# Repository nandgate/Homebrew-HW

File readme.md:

Hardware files for the 8-bit homebrew project.

* Each folder contains the KiCad project for a processor/board.
* Under the PLD there is a folder with the WinCUPL projects for the PLD for each board.

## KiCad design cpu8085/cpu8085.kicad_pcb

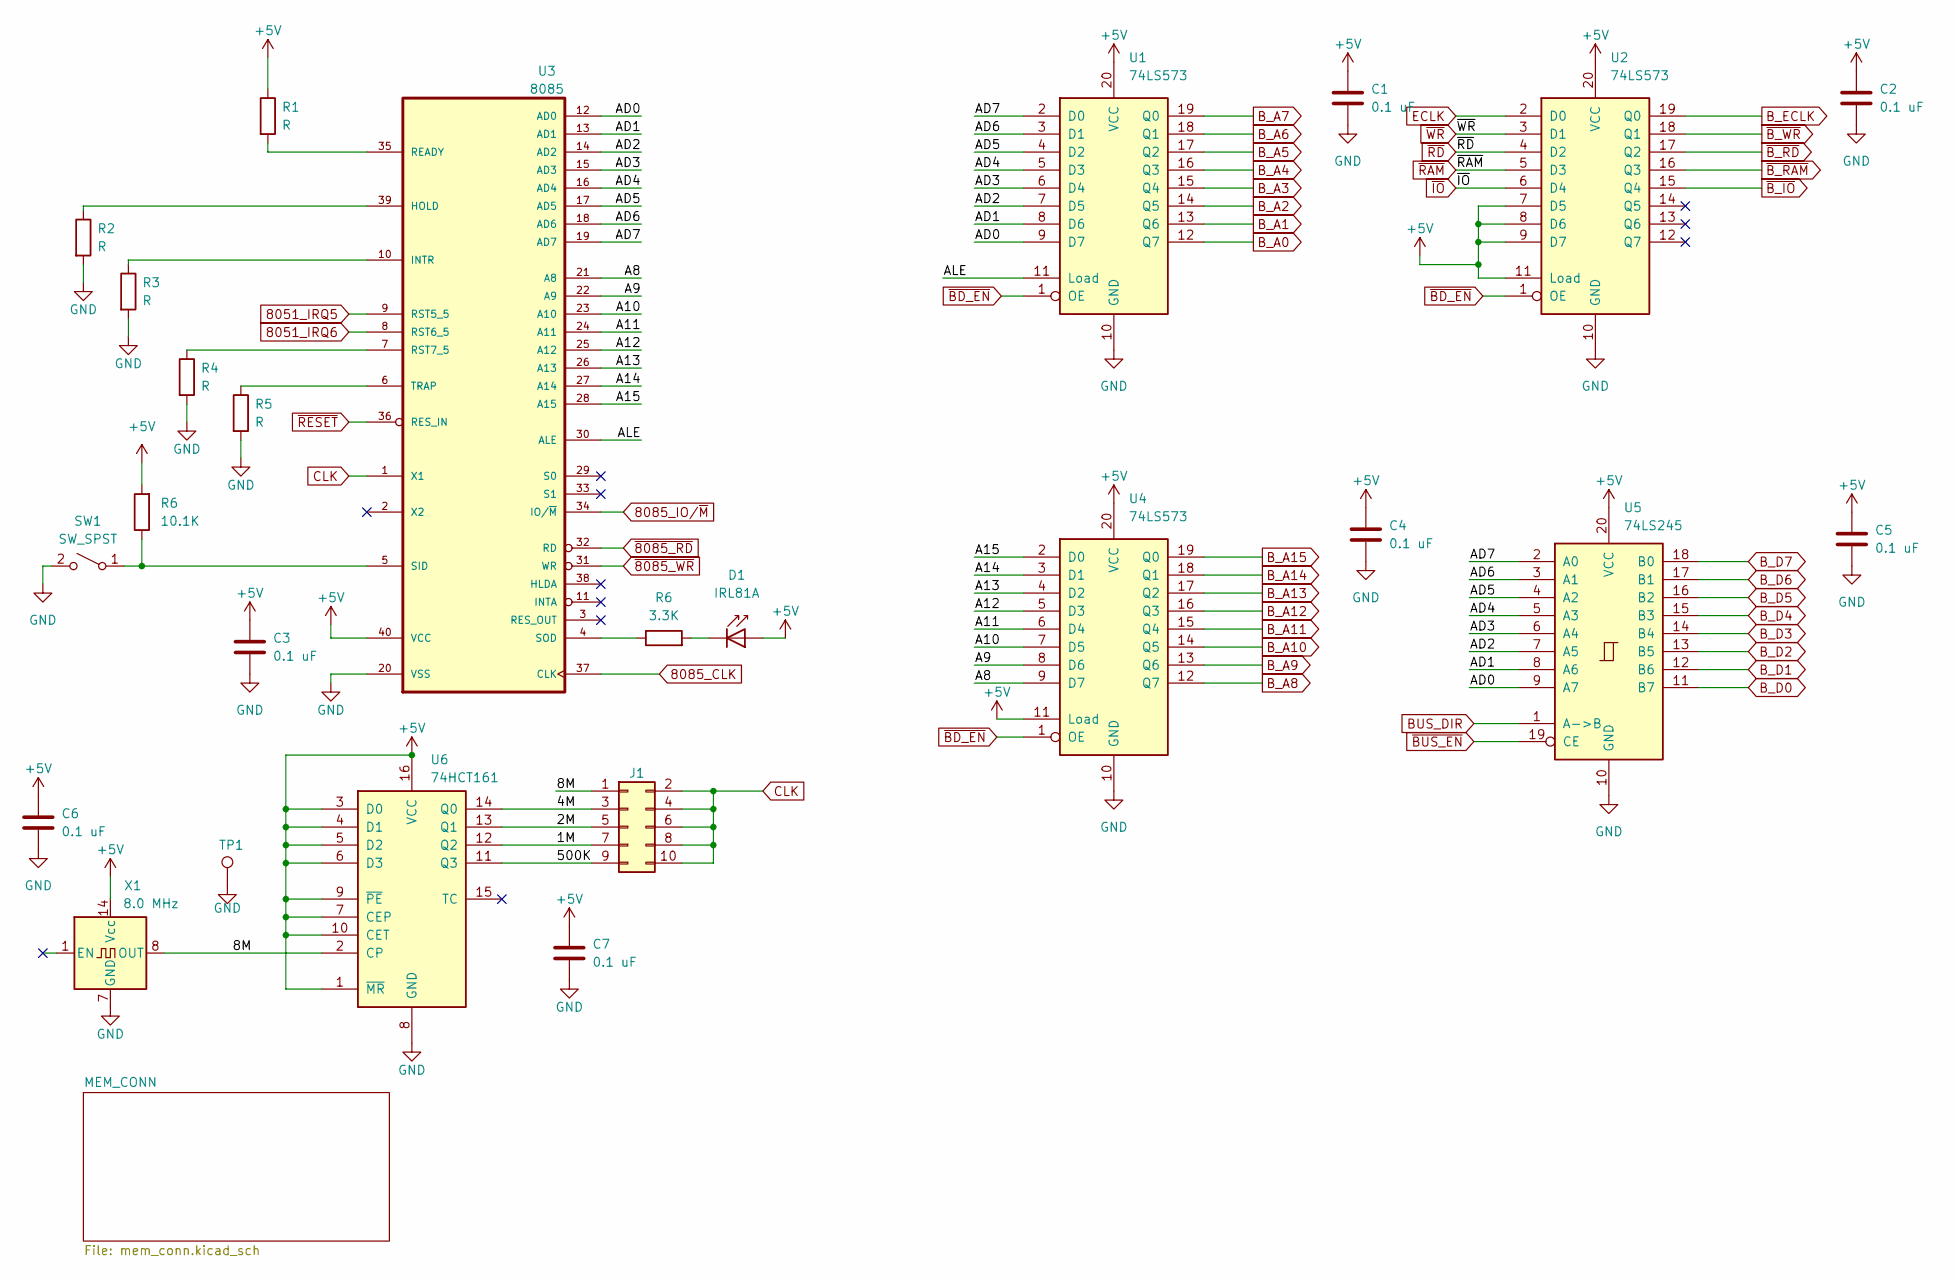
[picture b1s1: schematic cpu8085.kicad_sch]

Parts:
C1, C2, C3, C4, C5, C6, C7: 0.1 uF; C_Rect_L7.2mm_W3.0mm_P5.00mm_FKS2_FKP2_MKS2_MKP2
D1: IRL81A; LED_D5.0mm
J1: Conn_02x05_Odd_Even; PinHeader_2x05_P2.54mm_Vertical
R1, R2, R3, R4, R5: R; R_Axial_DIN0207_L6.3mm_D2.5mm_P10.16mm_Horizontal
R6: 10.1K; R_Axial_DIN0207_L6.3mm_D2.5mm_P10.16mm_Horizontal
SW1: SW_SPST; SW_DIP_SPSTx01_Slide_9.78x4.72mm_W7.62mm_P2.54mm
TP1: TestPoint; TestPoint_Pad_2.0x2.0mm
U1, U2, U4: 74LS573; DIP-20_W7.62mm
U3: 8085; DIP-40_W15.24mm_Socket
U5: 74LS245; DIP-20_W7.62mm
U6: 74HCT161; DIP-16_W7.62mm
X1: 8.0 MHz; Oscillator_DIP-14

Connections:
8051_IRQ5: U3.9 (RST5_5); also elsewhere on the board
8051_IRQ6: U3.8 (RST6_5); also elsewhere on the board
8085_CLK: U3.37 (CLK); also elsewhere on the board
8085_IO/~M: U3.34 (IO/~M); also elsewhere on the board
/1M: J1.7, U6.12 (Q2)
/2M: J1.5, U6.13 (Q1)
/4M: J1.3, U6.14 (Q0)
/8M: J1.1, U6.2 (CP), X1.8 (OUT)
/500K: J1.9, U6.11 (Q3)
/A8: U3.21 (A8), U4.9 (D7)
/A9: U3.22 (A9), U4.8 (D6)
/A10: U3.23 (A10), U4.7 (D5)
/A11: U3.24 (A11), U4.6 (D4)
/A12: U3.25 (A12), U4.5 (D3)
/A13: U3.26 (A13), U4.4 (D2)
/A14: U3.27 (A14), U4.3 (D1)
/A15: U3.28 (A15), U4.2 (D0)
/AD0: U1.9 (D7), U3.12 (AD0), U5.9 (A7)
/AD1: U1.8 (D6), U3.13 (AD1), U5.8 (A6)
/AD2: U1.7 (D5), U3.14 (AD2), U5.7 (A5)
/AD3: U1.6 (D4), U3.15 (AD3), U5.6 (A4)
/AD4: U1.5 (D3), U3.16 (AD4), U5.5 (A3)
/AD5: U1.4 (D2), U3.17 (AD5), U5.4 (A2)
/AD6: U1.3 (D1), U3.18 (AD6), U5.3 (A1)
/AD7: U1.2 (D0), U3.19 (AD7), U5.2 (A0)
/ALE: U1.11 (Load), U3.30 (ALE)
BUS_DIR: U5.1 (A->B); also elsewhere on the board
B_A0: U1.12 (Q7); also elsewhere on the board
B_A1: U1.13 (Q6); also elsewhere on the board
B_A2: U1.14 (Q5); also elsewhere on the board
B_A3: U1.15 (Q4); also elsewhere on the board
B_A4: U1.16 (Q3); also elsewhere on the board
B_A5: U1.17 (Q2); also elsewhere on the board
B_A6: U1.18 (Q1); also elsewhere on the board
B_A7: U1.19 (Q0); also elsewhere on the board
B_A8: U4.12 (Q7); also elsewhere on the board
B_A9: U4.13 (Q6); also elsewhere on the board
B_A10: U4.14 (Q5); also elsewhere on the board
B_A11: U4.15 (Q4); also elsewhere on the board
B_A12: U4.16 (Q3); also elsewhere on the board
B_A13: U4.17 (Q2); also elsewhere on the board
B_A14: U4.18 (Q1); also elsewhere on the board
B_A15: U4.19 (Q0); also elsewhere on the board
B_D0: U5.11 (B7); also elsewhere on the board
B_D1: U5.12 (B6); also elsewhere on the board
B_D2: U5.13 (B5); also elsewhere on the board
B_D3: U5.14 (B4); also elsewhere on the board
B_D4: U5.15 (B3); also elsewhere on the board
B_D5: U5.16 (B2); also elsewhere on the board
B_D6: U5.17 (B1); also elsewhere on the board
B_D7: U5.18 (B0); also elsewhere on the board
B_ECLK: U2.19 (Q0); also elsewhere on the board
CLK: J1.2, J1.4, J1.6, J1.8, J1.10, U3.1 (X1)
ECLK: U2.2 (D0); also elsewhere on the board
GND: C1.2, C2.2, C3.2, C4.2, C5.2, C6.2, C7.2, R2.2, R3.2, R4.2, R5.2, SW1.2 (B), TP1.1, U1.10 (GND), U2.10 (GND), U3.20 (VSS), U4.10 (GND), U5.10 (GND), U6.8 (GND), X1.7 (GND); also elsewhere on the board
unnamed: R2.1, U3.39 (HOLD)
unnamed: R3.1, U3.10 (INTR)
unnamed: R1.2, U3.35 (READY)
unnamed: R4.1, U3.7 (RST7_5)
unnamed: R5.1, U3.6 (TRAP)
~8085_RD: U3.32 (RD); also elsewhere on the board
~8085_WR: U3.31 (WR); also elsewhere on the board
~BD_EN: U1.1 (OE), U2.1 (OE), U4.1 (OE); also elsewhere on the board
~BUS_EN: U5.19 (CE); also elsewhere on the board
~B_IO: U2.15 (Q4); also elsewhere on the board
~B_RAM: U2.16 (Q3); also elsewhere on the board
~B_RD: U2.17 (Q2); also elsewhere on the board
~B_WR: U2.18 (Q1); also elsewhere on the board
~IO: U2.6 (D4); also elsewhere on the board
~RAM: U2.5 (D3); also elsewhere on the board
~RD: U2.4 (D2); also elsewhere on the board
~RESET: U3.36 (RES_IN); also elsewhere on the board
~WR: U2.3 (D1); also elsewhere on the board

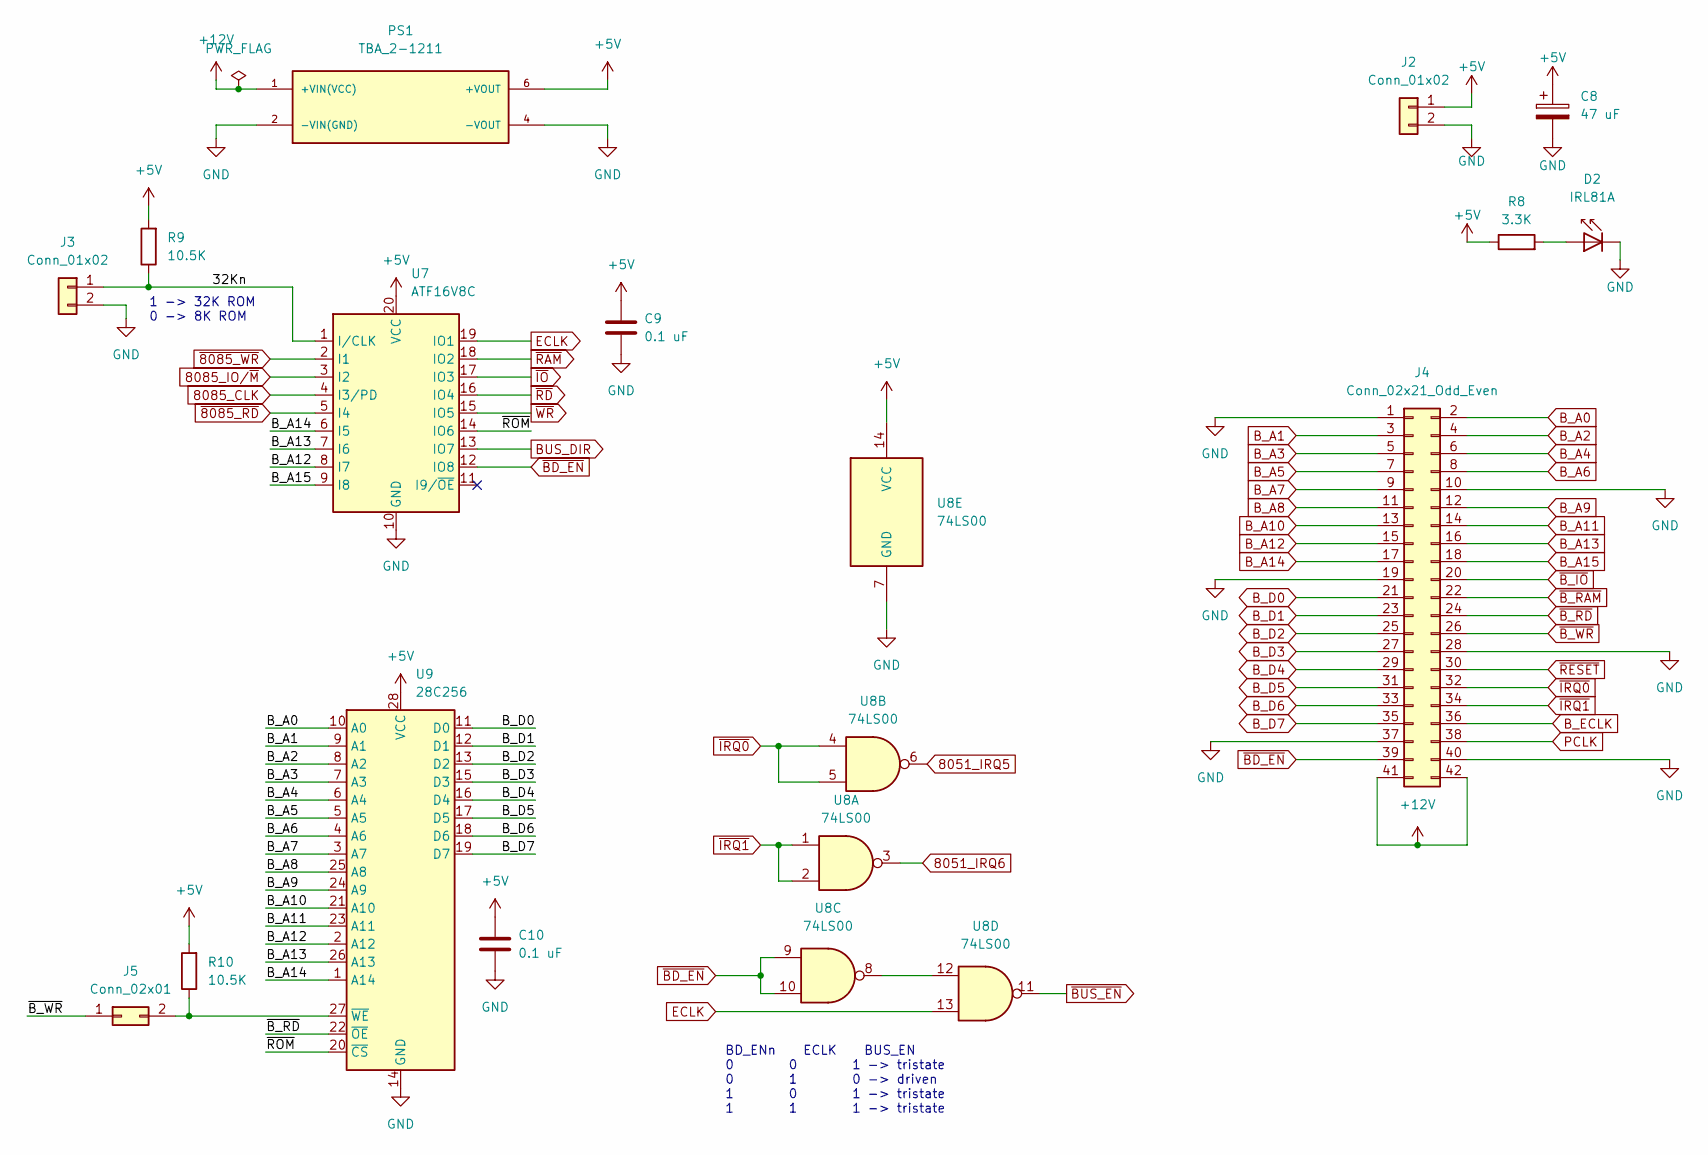
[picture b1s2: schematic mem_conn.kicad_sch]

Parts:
C8: 47 uF; CP_Radial_D5.0mm_P2.00mm
C9, C10: 0.1 uF; C_Rect_L7.2mm_W3.0mm_P5.00mm_FKS2_FKP2_MKS2_MKP2
D2: IRL81A; LED_D5.0mm
J2, J3: Conn_01x02; PinHeader_1x02_P2.54mm_Vertical
J4: Conn_02x21_Odd_Even; PinHeader_2x21_P2.54mm_Vertical
J5: Conn_02x01; PinHeader_1x02_P2.54mm_Vertical
PS1: TBA_2-1211; CONV_TBA_2-1211; PARTREV April 19, 2021
R8: 3.3K; R_Axial_DIN0207_L6.3mm_D2.5mm_P10.16mm_Horizontal
R9, R10: 10.5K; R_Axial_DIN0207_L6.3mm_D2.5mm_P10.16mm_Horizontal
U7: ATF16V8C; DIP-20_W7.62mm
U8: 74LS00; DIP-14_W7.62mm
U9: 28C256; DIP-28_W15.24mm

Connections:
8051_IRQ5: U8.6; also elsewhere on the board
8051_IRQ6: U8.3; also elsewhere on the board
8085_CLK: U7.4 (I3/PD); also elsewhere on the board
8085_IO/~M: U7.3 (I2); also elsewhere on the board
+12V: J4.41, J4.42, PS1.1 (+VIN(VCC))
/MEM_CONN/32Kn: J3.1, R9.1, U7.1 (I/CLK)
/MEM_CONN/~ROM: U7.14 (IO6), U9.20 (~CS)
BUS_DIR: U7.13 (IO7); also elsewhere on the board
B_A0: J4.2, U9.10 (A0); also elsewhere on the board
B_A1: J4.3, U9.9 (A1); also elsewhere on the board
B_A2: J4.4, U9.8 (A2); also elsewhere on the board
B_A3: J4.5, U9.7 (A3); also elsewhere on the board
B_A4: J4.6, U9.6 (A4); also elsewhere on the board
B_A5: J4.7, U9.5 (A5); also elsewhere on the board
B_A6: J4.8, U9.4 (A6); also elsewhere on the board
B_A7: J4.9, U9.3 (A7); also elsewhere on the board
B_A8: J4.11, U9.25 (A8); also elsewhere on the board
B_A9: J4.12, U9.24 (A9); also elsewhere on the board
B_A10: J4.13, U9.21 (A10); also elsewhere on the board
B_A11: J4.14, U9.23 (A11); also elsewhere on the board
B_A12: J4.15, U7.8 (I7), U9.2 (A12); also elsewhere on the board
B_A13: J4.16, U7.7 (I6), U9.26 (A13); also elsewhere on the board
B_A14: J4.17, U7.6 (I5), U9.1 (A14); also elsewhere on the board
B_A15: J4.18, U7.9 (I8); also elsewhere on the board
B_D0: J4.21, U9.11 (D0); also elsewhere on the board
B_D1: J4.23, U9.12 (D1); also elsewhere on the board
B_D2: J4.25, U9.13 (D2); also elsewhere on the board
B_D3: J4.27, U9.15 (D3); also elsewhere on the board
B_D4: J4.29, U9.16 (D4); also elsewhere on the board
B_D5: J4.31, U9.17 (D5); also elsewhere on the board
B_D6: J4.33, U9.18 (D6); also elsewhere on the board
B_D7: J4.35, U9.19 (D7); also elsewhere on the board
B_ECLK: J4.36; also elsewhere on the board
ECLK: U7.19 (IO1), U8.13; also elsewhere on the board
GND: C8.2, C9.2, C10.2, D2.1 (K), J2.2, J3.2, J4.1, J4.10, J4.19, J4.28, J4.37, J4.40, PS1.2 (-VIN(GND)), PS1.4 (-VOUT), U7.10 (GND), U8.7 (GND), U9.14 (GND); also elsewhere on the board
unnamed: D2.2 (A), R8.2
unnamed: J5.2, R10.1, U9.27 (~WE)
unnamed: U8.8, U8.12
PCLK: J4.38
~8085_RD: U7.5 (I4); also elsewhere on the board
~8085_WR: U7.2 (I1); also elsewhere on the board
~BD_EN: J4.39, U7.12 (IO8), U8.9, U8.10; also elsewhere on the board
~BUS_EN: U8.11; also elsewhere on the board
~B_IO: J4.20; also elsewhere on the board
~B_RAM: J4.22; also elsewhere on the board
~B_RD: J4.24, U9.22 (~OE); also elsewhere on the board
~B_WR: J4.26, J5.1; also elsewhere on the board
~IO: U7.17 (IO3); also elsewhere on the board
~IRQ0: J4.32, U8.4, U8.5
~IRQ1: J4.34, U8.1, U8.2
~RAM: U7.18 (IO2); also elsewhere on the board
~RD: U7.16 (IO4); also elsewhere on the board
~RESET: J4.30; also elsewhere on the board
~WR: U7.15 (IO5); also elsewhere on the board

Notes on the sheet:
1 -> 32K ROM 0 -> 8K ROM
BD_ENn ECLK BUS_EN 0 0 1 -> tristate 0 1 0 -> driven 1 0 1 -> tristate 1 1 1 -> tristate

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
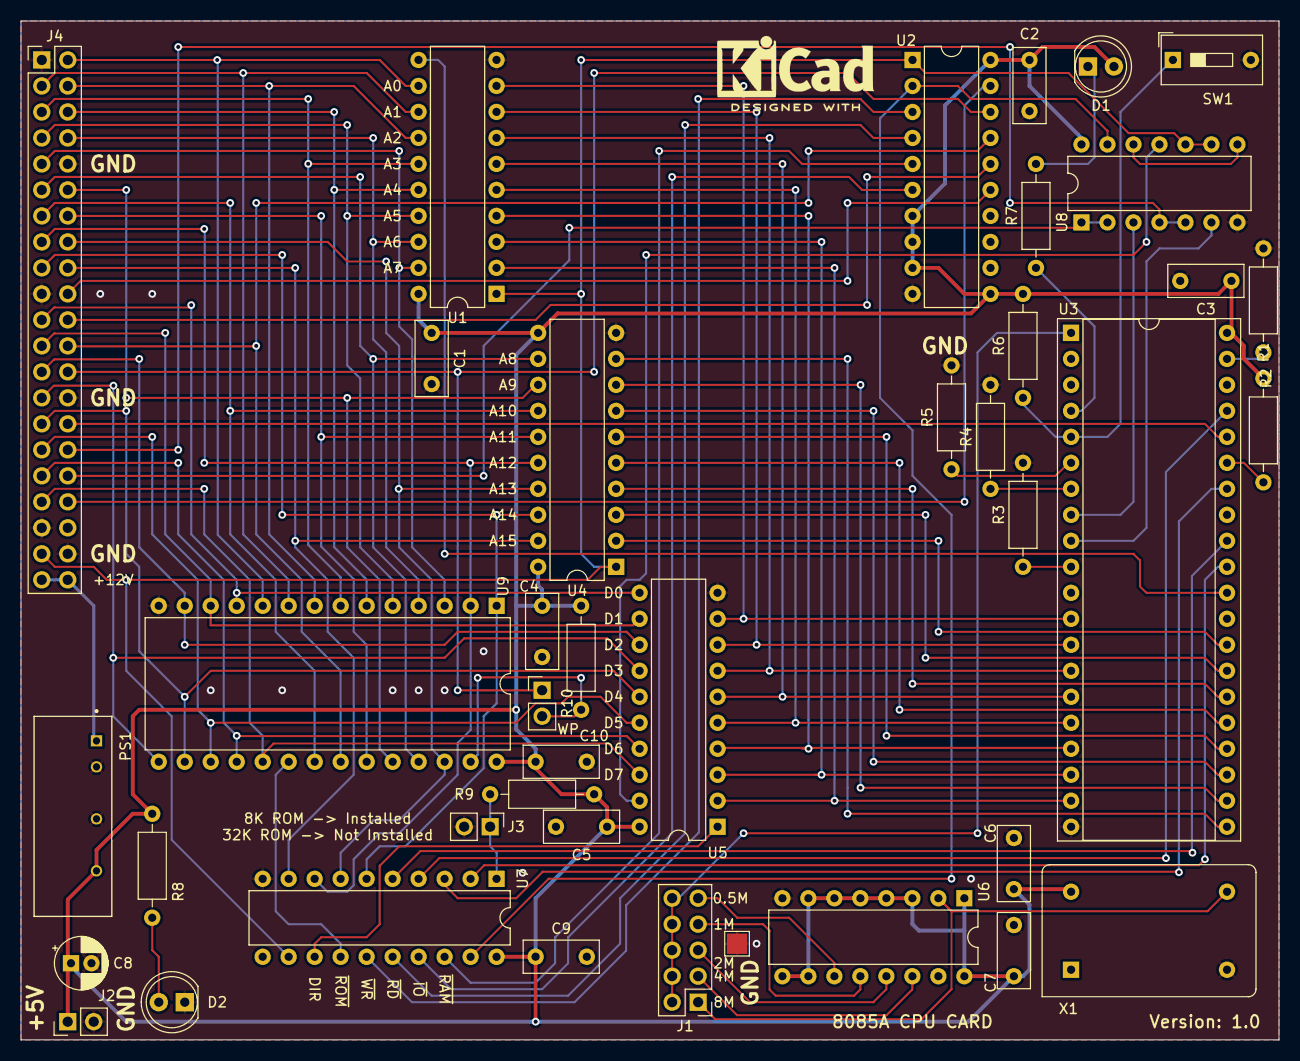
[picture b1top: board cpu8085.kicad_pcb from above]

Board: 2 copper layers, 122.9 x 99.6 mm, 40 parts (0 on the bottom side), 85 nets.

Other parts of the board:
R7: 3.3K; R_Axial_DIN0207_L6.3mm_D2.5mm_P10.16mm_Horizontal

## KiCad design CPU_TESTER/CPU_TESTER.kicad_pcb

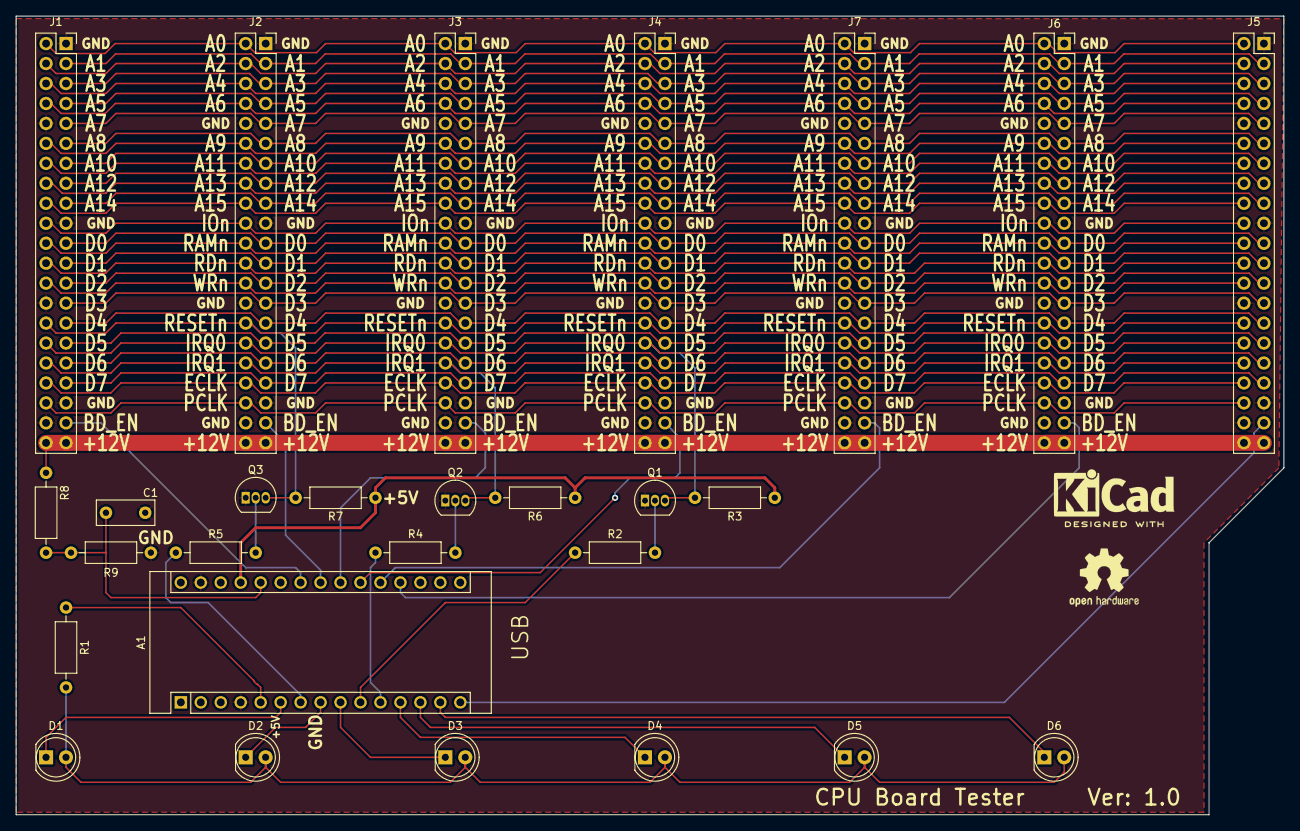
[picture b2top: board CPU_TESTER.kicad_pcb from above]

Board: 2 copper layers, 161.3 x 101.6 mm, 27 parts (0 on the bottom side), 58 nets.

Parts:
A1: Arduino_Nano_v3.x; Arduino_Nano
C1: 0.1uF; C_Rect_L7.2mm_W3.0mm_P5.00mm_FKS2_FKP2_MKS2_MKP2
D1, D2, D3, D4, D5, D6: BiColorLED_RG; LED_D5.0mm_FlatTop
J1, J2, J3, J4, J5, J6, J7: Conn_02x21_Odd_Even; PinSocket_2x21_P2.54mm_Vertical
Q1, Q2, Q3: 2N3904; TO-92_Inline
R1, R8, R9: R; R_Axial_DIN0207_L6.3mm_D2.5mm_P10.16mm_Horizontal
R2, R3, R4, R5, R6, R7: 10.1K; R_Axial_DIN0207_L6.3mm_D2.5mm_P10.16mm_Horizontal

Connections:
+5V: A1.27 (+5V), R3.1, R6.1, R7.1
+12V: J1.41, J1.42, J2.41, J2.42, J3.41, J3.42, J4.41, J4.42, J5.41, J5.42, J6.41, J6.42, J7.41, J7.42, R8.1
/12V_MON: A1.26 (A7), C1.1, R8.2, R9.1
/IRQ_0: A1.10 (D7), R2.1
/IRQ_1: A1.11 (D8), R4.1
/LED_0: A1.6 (D3), D1.1
/LED_1: A1.8 (D5), D2.1
/LED_2: A1.9 (D6), D3.1
/LED_3: A1.12 (D9), D4.1
/LED_4: A1.13 (D10), D5.1
/LED_5: A1.14 (D11), D6.1
/LED_C: A1.5 (D2), R1.1
/RST: A1.7 (D4), R5.1
A0: J1.2, J2.2, J3.2, J4.2, J5.2, J6.2, J7.2
A1: J1.3, J2.3, J3.3, J4.3, J5.3, J6.3, J7.3
A2: J1.4, J2.4, J3.4, J4.4, J5.4, J6.4, J7.4
A3: J1.5, J2.5, J3.5, J4.5, J5.5, J6.5, J7.5
A4: J1.6, J2.6, J3.6, J4.6, J5.6, J6.6, J7.6
A5: J1.7, J2.7, J3.7, J4.7, J5.7, J6.7, J7.7
A6: J1.8, J2.8, J3.8, J4.8, J5.8, J6.8, J7.8
A7: J1.9, J2.9, J3.9, J4.9, J5.9, J6.9, J7.9
A8: J1.11, J2.11, J3.11, J4.11, J5.11, J6.11, J7.11
A9: J1.12, J2.12, J3.12, J4.12, J5.12, J6.12, J7.12
A10: J1.13, J2.13, J3.13, J4.13, J5.13, J6.13, J7.13
A11: J1.14, J2.14, J3.14, J4.14, J5.14, J6.14, J7.14
A12: J1.15, J2.15, J3.15, J4.15, J5.15, J6.15, J7.15
A13: J1.16, J2.16, J3.16, J4.16, J5.16, J6.16, J7.16
A14: J1.17, J2.17, J3.17, J4.17, J5.17, J6.17, J7.17
A15: J1.18, J2.18, J3.18, J4.18, J5.18, J6.18, J7.18
BD_EN0: A1.24 (A5), J1.39
BD_EN1: A1.23 (A4), J2.39
BD_EN2: A1.22 (A3), J3.39
BD_EN3: A1.21 (A2), J4.39
BD_EN4: A1.20 (A1), J7.39
BD_EN5: A1.19 (A0), J6.39
BD_ENM: A1.15 (D12), J5.39
D0: J1.21, J2.21, J3.21, J4.21, J5.21, J6.21, J7.21
D1: J1.23, J2.23, J3.23, J4.23, J5.23, J6.23, J7.23
D2: J1.25, J2.25, J3.25, J4.25, J5.25, J6.25, J7.25
D3: J1.27, J2.27, J3.27, J4.27, J5.27, J6.27, J7.27
D4: J1.29, J2.29, J3.29, J4.29, J5.29, J6.29, J7.29
D5: J1.31, J2.31, J3.31, J4.31, J5.31, J6.31, J7.31
D6: J1.33, J2.33, J3.33, J4.33, J5.33, J6.33, J7.33
D7: J1.35, J2.35, J3.35, J4.35, J5.35, J6.35, J7.35
ECLK: J1.36, J2.36, J3.36, J4.36, J5.36, J6.36, J7.36
GND: A1.4 (GND), A1.29 (GND), C1.2, J1.1, J1.10, J1.19, J1.28, J1.37, J1.40, J2.1, J2.10, J2.19, J2.28, J2.37, J2.40, J3.1, J3.10, J3.19, J3.28, J3.37, J3.40, J4.1, J4.10, J4.19, J4.28, J4.37, J4.40, J5.1, J5.10, J5.19, J5.28, J5.37, J5.40, J6.1, J6.10, J6.19, J6.28, J6.37, J6.40, J7.1, J7.10, J7.19, J7.28, J7.37, J7.40, Q1.1 (E), Q2.1 (E), Q3.1 (E), R9.2
IRQ0: J1.32, J2.32, J3.32, J4.32, J5.32, J6.32, J7.32, Q1.3 (C), R3.2
IRQ1: J1.34, J2.34, J3.34, J4.34, J5.34, J6.34, J7.34, Q2.3 (C), R6.2
unnamed: D1.2, D2.2, D3.2, D4.2, D5.2, D6.2, R1.2
unnamed: Q1.2 (B), R2.2
unnamed: Q2.2 (B), R4.2
unnamed: Q3.2 (B), R5.2
PCLK: J1.38, J2.38, J3.38, J4.38, J5.38, J6.38, J7.38
~IO: J1.20, J2.20, J3.20, J4.20, J5.20, J6.20, J7.20
~RAM: J1.22, J2.22, J3.22, J4.22, J5.22, J6.22, J7.22
~RD: J1.24, J2.24, J3.24, J4.24, J5.24, J6.24, J7.24
~RESET: J1.30, J2.30, J3.30, J4.30, J5.30, J6.30, J7.30, Q3.3 (C), R7.2
~WR: J1.26, J2.26, J3.26, J4.26, J5.26, J6.26, J7.26

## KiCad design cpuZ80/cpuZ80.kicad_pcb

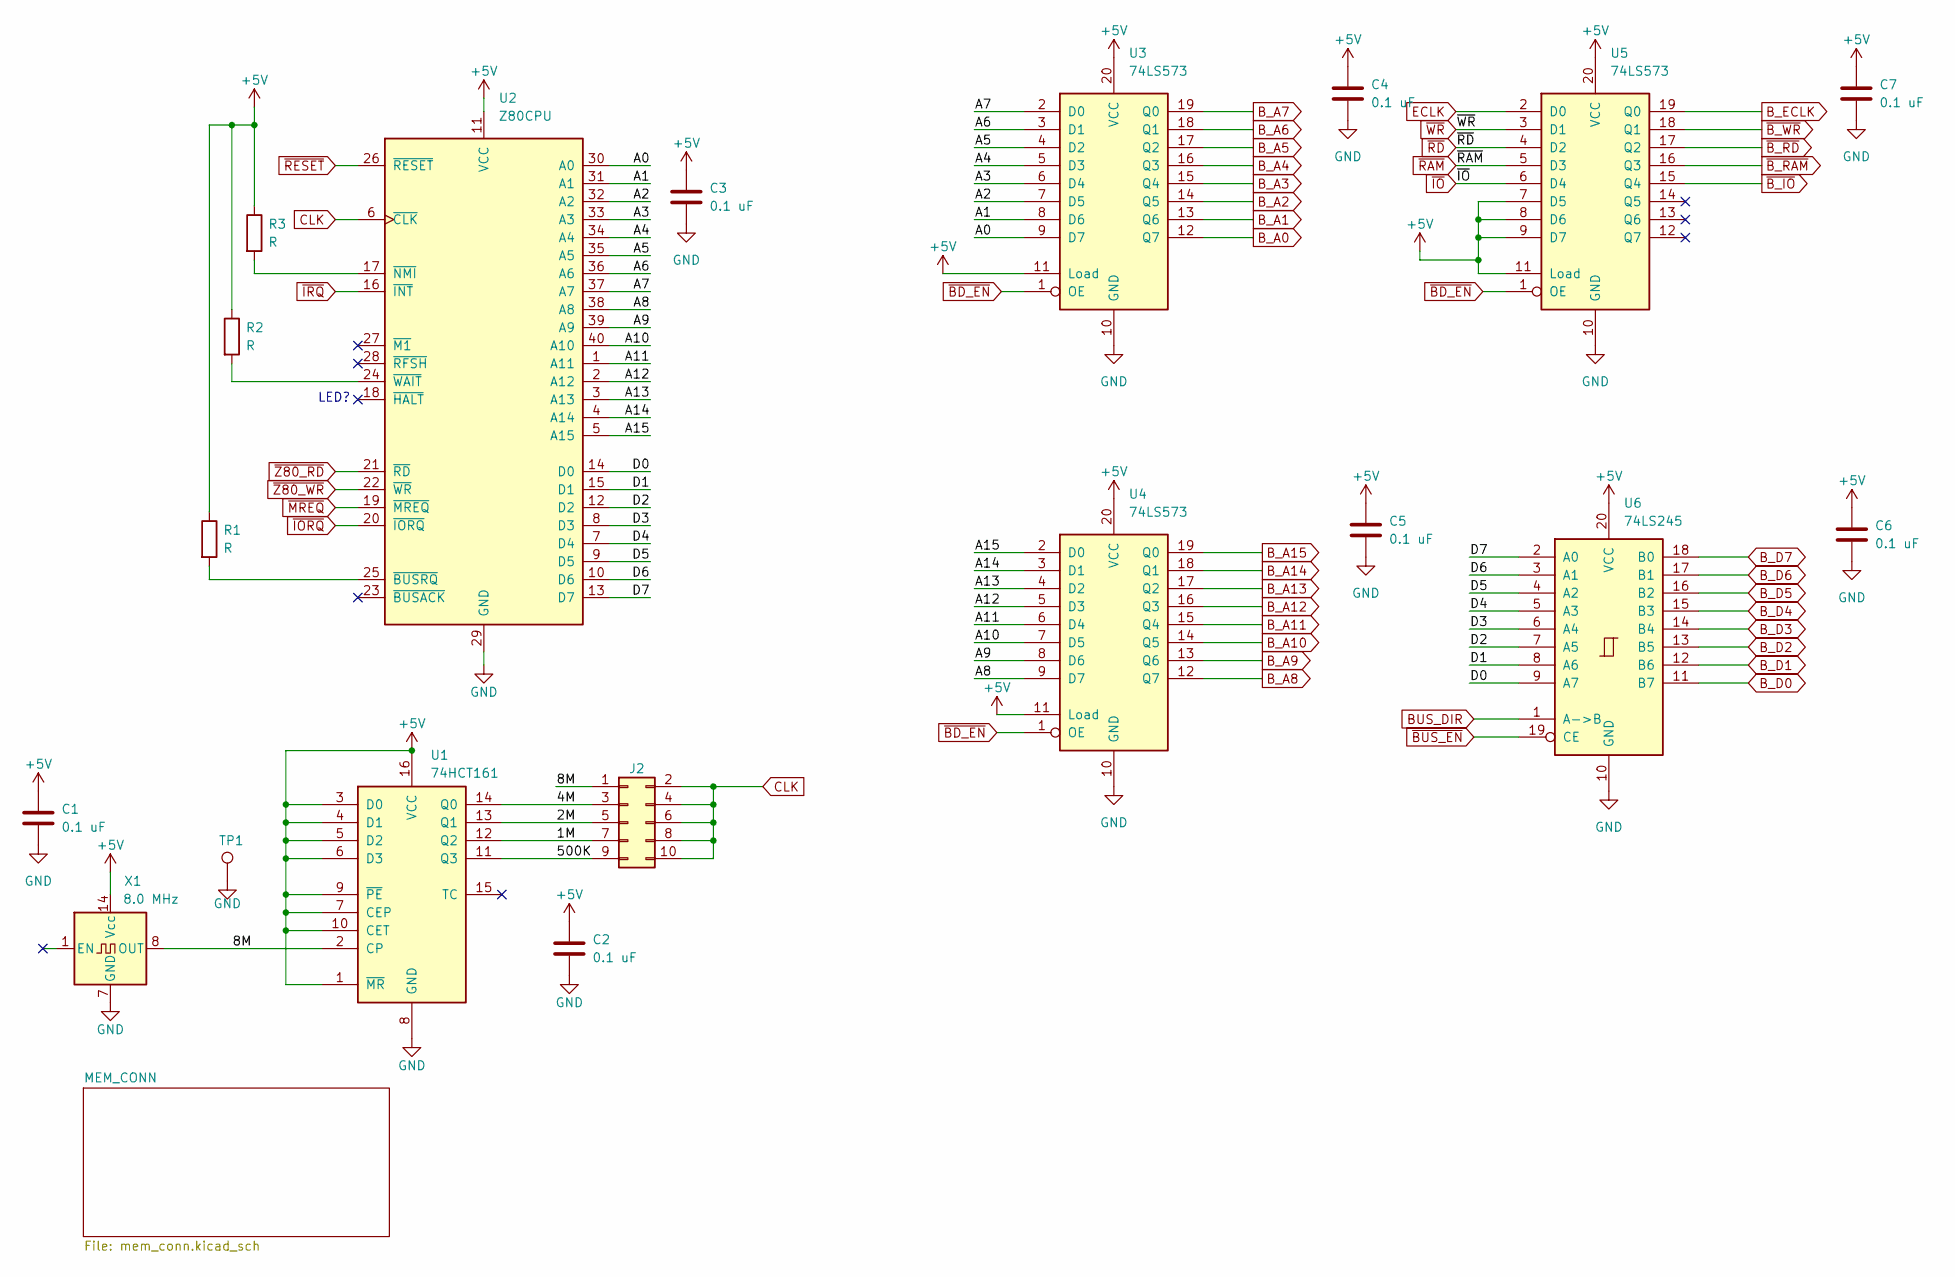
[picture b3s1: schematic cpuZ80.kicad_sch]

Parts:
C1, C2, C3, C4, C5, C6, C7: 0.1 uF; C_Rect_L7.2mm_W3.0mm_P5.00mm_FKS2_FKP2_MKS2_MKP2
J2: Conn_02x05_Odd_Even; PinHeader_2x05_P2.54mm_Vertical
R1, R2, R3: R; R_Axial_DIN0207_L6.3mm_D2.5mm_P10.16mm_Horizontal
TP1: TestPoint; TestPoint_Pad_2.0x2.0mm
U1: 74HCT161; DIP-16_W7.62mm
U2: Z80CPU; DIP-40_W15.24mm
U3, U4, U5: 74LS573; DIP-20_W7.62mm
U6: 74LS245; DIP-20_W7.62mm
X1: 8.0 MHz; Oscillator_DIP-14

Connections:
+5V: C1.1, C2.1, C3.1, C4.1, C5.1, C6.1, C7.1, R1.1, R2.1, R3.1, U1.1 (~MR), U1.3 (D0), U1.4 (D1), U1.5 (D2), U1.6 (D3), U1.7 (CEP), U1.9 (~PE), U1.10 (CET), U1.16 (VCC), U2.11 (VCC), U3.11 (Load), U3.20 (VCC), U4.11 (Load), U4.20 (VCC), U5.7 (D5), U5.8 (D6), U5.9 (D7), U5.11 (Load), U5.20 (VCC), U6.20 (VCC), X1.14 (Vcc); also elsewhere on the board
/1M: J2.7, U1.12 (Q2)
/2M: J2.5, U1.13 (Q1)
/4M: J2.3, U1.14 (Q0)
/8M: J2.1, U1.2 (CP), X1.8 (OUT)
/500K: J2.9, U1.11 (Q3)
/A0: U2.30 (A0), U3.9 (D7)
/A1: U2.31 (A1), U3.8 (D6)
/A2: U2.32 (A2), U3.7 (D5)
/A3: U2.33 (A3), U3.6 (D4)
/A4: U2.34 (A4), U3.5 (D3)
/A5: U2.35 (A5), U3.4 (D2)
/A6: U2.36 (A6), U3.3 (D1)
/A7: U2.37 (A7), U3.2 (D0)
/A8: U2.38 (A8), U4.9 (D7)
/A9: U2.39 (A9), U4.8 (D6)
/A10: U2.40 (A10), U4.7 (D5)
/A11: U2.1 (A11), U4.6 (D4)
/A12: U2.2 (A12), U4.5 (D3)
/A13: U2.3 (A13), U4.4 (D2)
/A14: U2.4 (A14), U4.3 (D1)
/A15: U2.5 (A15), U4.2 (D0)
/D0: U2.14 (D0), U6.9 (A7)
/D1: U2.15 (D1), U6.8 (A6)
/D2: U2.12 (D2), U6.7 (A5)
/D3: U2.8 (D3), U6.6 (A4)
/D4: U2.7 (D4), U6.5 (A3)
/D5: U2.9 (D5), U6.4 (A2)
/D6: U2.10 (D6), U6.3 (A1)
/D7: U2.13 (D7), U6.2 (A0)
BUS_DIR: U6.1 (A->B); also elsewhere on the board
B_A0: U3.12 (Q7); also elsewhere on the board
B_A1: U3.13 (Q6); also elsewhere on the board
B_A2: U3.14 (Q5); also elsewhere on the board
B_A3: U3.15 (Q4); also elsewhere on the board
B_A4: U3.16 (Q3); also elsewhere on the board
B_A5: U3.17 (Q2); also elsewhere on the board
B_A6: U3.18 (Q1); also elsewhere on the board
B_A7: U3.19 (Q0); also elsewhere on the board
B_A8: U4.12 (Q7); also elsewhere on the board
B_A9: U4.13 (Q6); also elsewhere on the board
B_A10: U4.14 (Q5); also elsewhere on the board
B_A11: U4.15 (Q4); also elsewhere on the board
B_A12: U4.16 (Q3); also elsewhere on the board
B_A13: U4.17 (Q2); also elsewhere on the board
B_A14: U4.18 (Q1); also elsewhere on the board
B_A15: U4.19 (Q0); also elsewhere on the board
B_D0: U6.11 (B7); also elsewhere on the board
B_D1: U6.12 (B6); also elsewhere on the board
B_D2: U6.13 (B5); also elsewhere on the board
B_D3: U6.14 (B4); also elsewhere on the board
B_D4: U6.15 (B3); also elsewhere on the board
B_D5: U6.16 (B2); also elsewhere on the board
B_D6: U6.17 (B1); also elsewhere on the board
B_D7: U6.18 (B0); also elsewhere on the board
B_ECLK: U5.19 (Q0); also elsewhere on the board
CLK: J2.2, J2.4, J2.6, J2.8, J2.10, U2.6 (~CLK); also elsewhere on the board
ECLK: U5.2 (D0); also elsewhere on the board
GND: C1.2, C2.2, C3.2, C4.2, C5.2, C6.2, C7.2, TP1.1, U1.8 (GND), U2.29 (GND), U3.10 (GND), U4.10 (GND), U5.10 (GND), U6.10 (GND), X1.7 (GND); also elsewhere on the board
unnamed: R3.2, U2.17 (~NMI)
unnamed: R2.2, U2.24 (~WAIT)
unnamed: R1.2, U2.25 (~BUSRQ)
~BD_EN: U3.1 (OE), U4.1 (OE), U5.1 (OE); also elsewhere on the board
~BUS_EN: U6.19 (CE); also elsewhere on the board
~B_IO: U5.15 (Q4); also elsewhere on the board
~B_RAM: U5.16 (Q3); also elsewhere on the board
~B_RD: U5.17 (Q2); also elsewhere on the board
~B_WR: U5.18 (Q1); also elsewhere on the board
~IORQ: U2.20 (~IORQ); also elsewhere on the board
~IO: U5.6 (D4); also elsewhere on the board
~IRQ: U2.16 (~INT); also elsewhere on the board
~MREQ: U2.19 (~MREQ); also elsewhere on the board
~RAM: U5.5 (D3); also elsewhere on the board
~RD: U5.4 (D2); also elsewhere on the board
~RESET: U2.26 (~RESET); also elsewhere on the board
~WR: U5.3 (D1); also elsewhere on the board
~Z80_RD: U2.21 (~RD); also elsewhere on the board
~Z80_WR: U2.22 (~WR); also elsewhere on the board

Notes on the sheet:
LED?

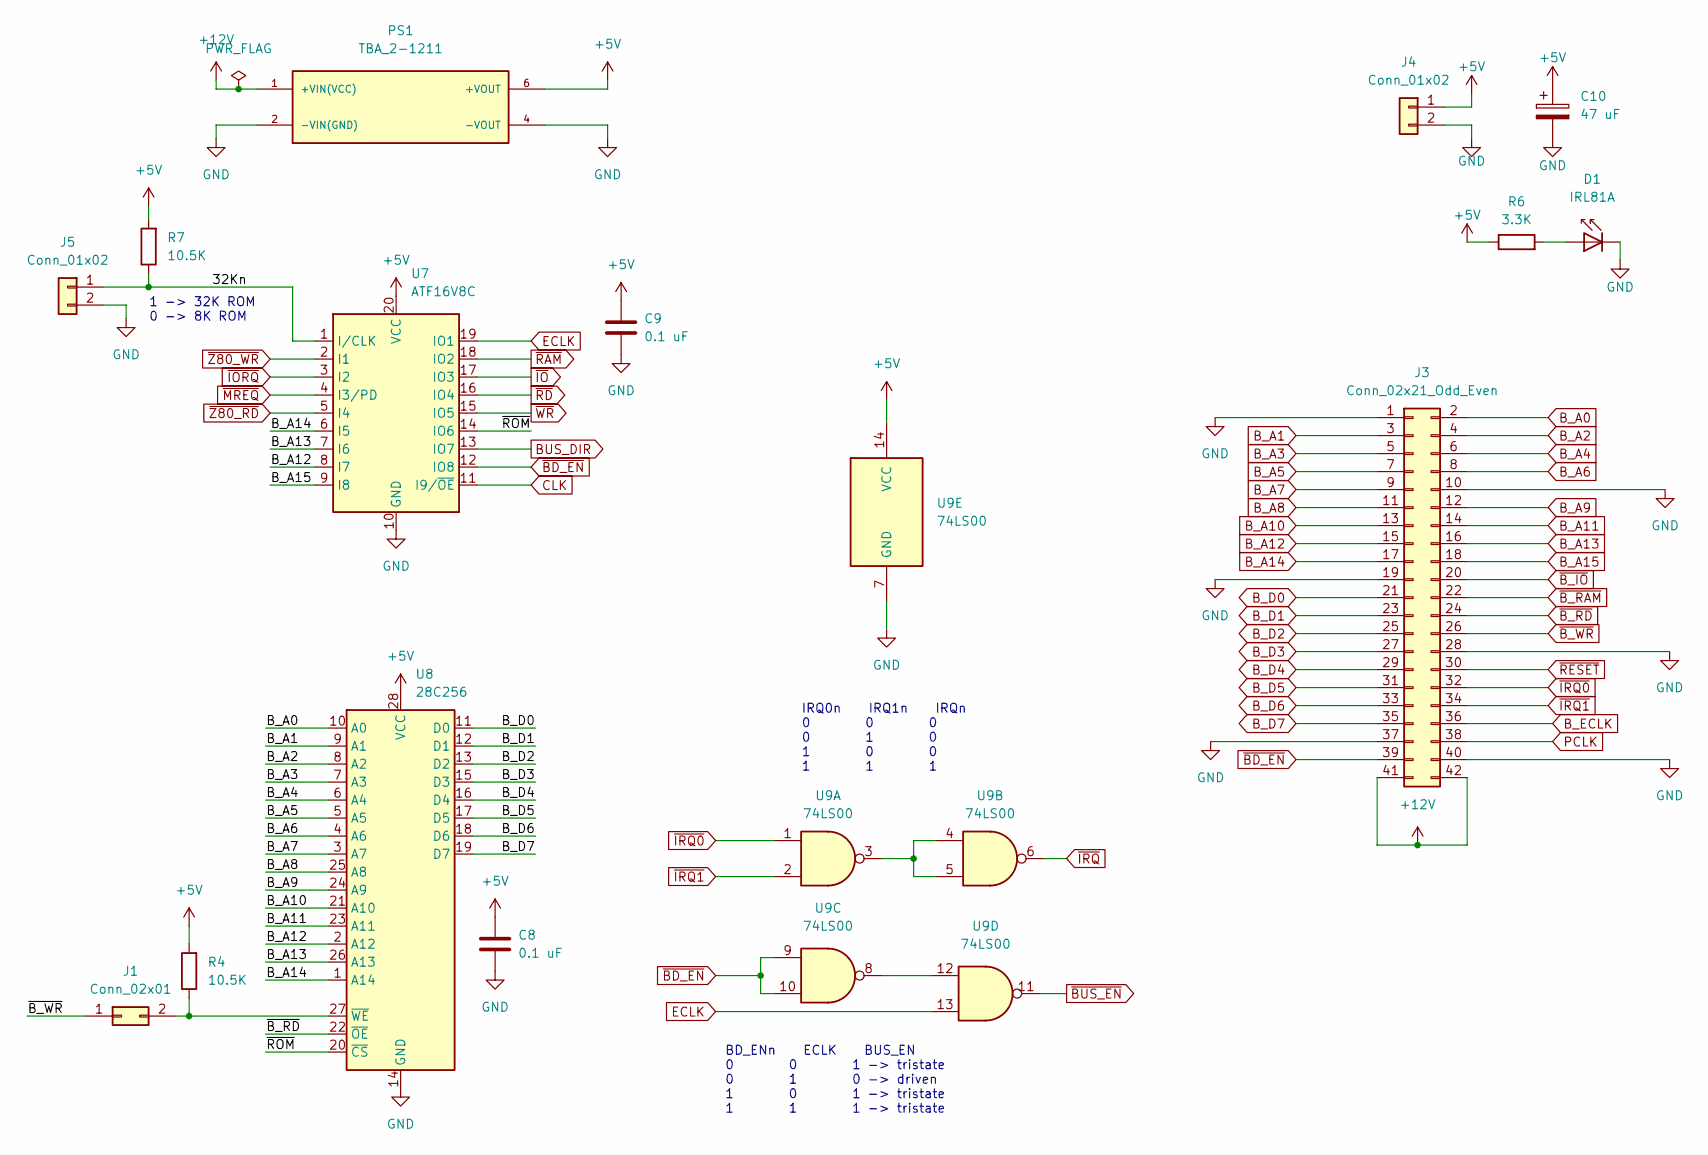
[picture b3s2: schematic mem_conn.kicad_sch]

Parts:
C8, C9: 0.1 uF; C_Rect_L7.2mm_W3.0mm_P5.00mm_FKS2_FKP2_MKS2_MKP2
C10: 47 uF; CP_Radial_D5.0mm_P2.00mm
D1: IRL81A; LED_D5.0mm
J1: Conn_02x01; PinHeader_1x02_P2.54mm_Vertical
J3: Conn_02x21_Odd_Even; PinHeader_2x21_P2.54mm_Vertical
J4, J5: Conn_01x02; PinHeader_1x02_P2.54mm_Vertical
PS1: TBA_2-1211; CONV_TBA_2-1211; PARTREV April 19, 2021
R4, R7: 10.5K; R_Axial_DIN0207_L6.3mm_D2.5mm_P10.16mm_Horizontal
R6: 3.3K; R_Axial_DIN0207_L6.3mm_D2.5mm_P10.16mm_Horizontal
U7: ATF16V8C; DIP-20_W7.62mm
U8: 28C256; DIP-28_W15.24mm
U9: 74LS00; DIP-14_W7.62mm

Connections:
+5V: C8.1, C9.1, C10.1, J4.1, PS1.6 (+VOUT), R4.2, R6.1, R7.2, U7.20 (VCC), U8.28 (VCC), U9.14 (VCC); also elsewhere on the board
+12V: J3.41, J3.42, PS1.1 (+VIN(VCC))
/MEM_CONN/32Kn: J5.1, R7.1, U7.1 (I/CLK)
/MEM_CONN/~ROM: U7.14 (IO6), U8.20 (~CS)
BUS_DIR: U7.13 (IO7); also elsewhere on the board
B_A0: J3.2, U8.10 (A0); also elsewhere on the board
B_A1: J3.3, U8.9 (A1); also elsewhere on the board
B_A2: J3.4, U8.8 (A2); also elsewhere on the board
B_A3: J3.5, U8.7 (A3); also elsewhere on the board
B_A4: J3.6, U8.6 (A4); also elsewhere on the board
B_A5: J3.7, U8.5 (A5); also elsewhere on the board
B_A6: J3.8, U8.4 (A6); also elsewhere on the board
B_A7: J3.9, U8.3 (A7); also elsewhere on the board
B_A8: J3.11, U8.25 (A8); also elsewhere on the board
B_A9: J3.12, U8.24 (A9); also elsewhere on the board
B_A10: J3.13, U8.21 (A10); also elsewhere on the board
B_A11: J3.14, U8.23 (A11); also elsewhere on the board
B_A12: J3.15, U7.8 (I7), U8.2 (A12); also elsewhere on the board
B_A13: J3.16, U7.7 (I6), U8.26 (A13); also elsewhere on the board
B_A14: J3.17, U7.6 (I5), U8.1 (A14); also elsewhere on the board
B_A15: J3.18, U7.9 (I8); also elsewhere on the board
B_D0: J3.21, U8.11 (D0); also elsewhere on the board
B_D1: J3.23, U8.12 (D1); also elsewhere on the board
B_D2: J3.25, U8.13 (D2); also elsewhere on the board
B_D3: J3.27, U8.15 (D3); also elsewhere on the board
B_D4: J3.29, U8.16 (D4); also elsewhere on the board
B_D5: J3.31, U8.17 (D5); also elsewhere on the board
B_D6: J3.33, U8.18 (D6); also elsewhere on the board
B_D7: J3.35, U8.19 (D7); also elsewhere on the board
B_ECLK: J3.36; also elsewhere on the board
CLK: U7.11 (I9/~OE); also elsewhere on the board
ECLK: U7.19 (IO1), U9.13; also elsewhere on the board
GND: C8.2, C9.2, C10.2, D1.1 (K), J3.1, J3.10, J3.19, J3.28, J3.37, J3.40, J4.2, J5.2, PS1.2 (-VIN(GND)), PS1.4 (-VOUT), U7.10 (GND), U8.14 (GND), U9.7 (GND); also elsewhere on the board
unnamed: D1.2 (A), R6.2
unnamed: J1.2, R4.1, U8.27 (~WE)
unnamed: U9.3, U9.4, U9.5
unnamed: U9.8, U9.12
PCLK: J3.38
~BD_EN: J3.39, U7.12 (IO8), U9.9, U9.10; also elsewhere on the board
~BUS_EN: U9.11; also elsewhere on the board
~B_IO: J3.20; also elsewhere on the board
~B_RAM: J3.22; also elsewhere on the board
~B_RD: J3.24, U8.22 (~OE); also elsewhere on the board
~B_WR: J1.1, J3.26; also elsewhere on the board
~IORQ: U7.3 (I2); also elsewhere on the board
~IO: U7.17 (IO3); also elsewhere on the board
~IRQ0: J3.32, U9.1
~IRQ1: J3.34, U9.2
~IRQ: U9.6; also elsewhere on the board
~MREQ: U7.4 (I3/PD); also elsewhere on the board
~RAM: U7.18 (IO2); also elsewhere on the board
~RD: U7.16 (IO4); also elsewhere on the board
~RESET: J3.30; also elsewhere on the board
~WR: U7.15 (IO5); also elsewhere on the board
~Z80_RD: U7.5 (I4); also elsewhere on the board
~Z80_WR: U7.2 (I1); also elsewhere on the board

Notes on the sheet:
1 -> 32K ROM 0 -> 8K ROM
IRQ0n IRQ1n IRQn 0 0 0 0 1 0 1 0 0 1 1 1
BD_ENn ECLK BUS_EN 0 0 1 -> tristate 0 1 0 -> driven 1 0 1 -> tristate 1 1 1 -> tristate

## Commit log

2022-08-10 Initial commit, .gitignore and MIT License.
2022-08-10 Design and layout for 6502/65C02/8602 processor board.
2022-08-10 Design and layout of the Main board (as built)
2022-08-10 Waveforms logic analyzer config file for IOBUS.
2022-08-13 Misc updates to PCB
2022-08-25 Moved devices around and size reduced board.
2022-08-25 Added PLD files for main board.
2022-08-25 Added PLD files for 6502.
2022-08-25 Added PLD files for 65C02.
2022-08-25 Added PLD files for 6802.
2022-08-25 Added README to PLD folders.
2022-08-25 Added readme file
2022-09-05 Removed .doc, .lst, .pdf for PLD prjects.
    These files are used for simulation. (.pdf is not a modern PDF but something else.)
2022-09-05 Fixed timing by remove ECLK sync.
2022-09-05 Fixed multiple issues
2022-09-05 Fixed RAM1 output state. Fixed IRQ polarity. Added BD_EN logic.
2022-09-05 Updated to as built.
2022-09-05 Updated PDF
2022-09-05 Updated .ignore
2022-09-19 Added Z80 CPU Board
2022-10-09 Created design files for CPU_TESTER
2022-10-13 Z80 PLD design files
2022-10-13 CPU tester design
2022-12-12 Updated tester schematic, per built
2022-12-12 Updated 65C02 PLD files, per built
2022-12-24 Updated voltage monitoring divider to as-built.
2022-12-24 Git cleanup
2022-12-24 Added PDF of schematic
2023-04-04 Added 8085 CPU
2023-04-04 Updated logic to improve timing
